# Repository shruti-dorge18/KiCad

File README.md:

# 📐KiCad PCB Design Projects

A collection of PCB designs created using **KiCad**, covering schematic design, PCB layout, footprint integration, and 3D visualization.

## 🛠️ Tools 

**KiCad**

## 🔗 Boardrepo 

PCB designs are also uploaded to **Boardrepo** for easy viewing without downloading or installing KiCad.

View my Boardrepo profile: https://boardrepo.com/shruti-dorge18

Each project in this repository includes its corresponding **Boardrepo link** for viewing the PCB design.

## 📋 Repository Contents 

Each project may include:

* `.kicad_sch` — Schematic
* `.kicad_pcb` — PCB layout
* `.kicad_pro` — KiCad project file
* Images — Schematic, PCB layout, and 3D views
* Footprints

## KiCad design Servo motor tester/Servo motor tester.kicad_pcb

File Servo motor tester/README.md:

# Servo Motor Tester – PCB Design

A PCB design for a servo motor tester circuit, created using KiCad.

## Overview

Designed a 555-timer-based PWM servo motor tester with an adjustable potentiometer for varying the PWM signal to sweep it through its range of motion.

The project was developed to practice PCB designing.

## Tools Used

* KiCad
* Snapmagic :  for downloading footprint & 3D model of potentiometer

## View PCB on Boardrepo
https://boardrepo.com/shruti-dorge18/servo-motor-tester

## Reference

This project was created while following this YouTube tutorial by Ampnics, for learning and reference:

https://youtu.be/3BYGPpejStI?si=WuTzUE_sMDbFLJ6_

## Project Structure

```text
Servo motor tester/
├── 3D model of potentiometer/
│   └── RD901F-40-15R1-B100K-00DL1.step
├── Footprints.pretty/
│   └── POT_RD901F-40-15R1-B100K-00DL1.kicad_mod
├── Images/
│   ├── 3Dview.png
│   ├── pcb.png
│   └── schematic.png
├── Servo motor tester.kicad_pcb
├── Servo motor tester.kicad_pro
└── Servo motor tester.kicad_sch
```

## Files

| File / Folder  | Description                                                   |
| -------------- | ------------------------------------------------------------- |
| `.kicad_sch`   | Circuit schematic                                             |
| `.kicad_pcb`   | PCB layout                                                    |
| `.kicad_pro`   | KiCad project file                                            |
| `Images/`      | Project images showing the schematic, PCB layout, and 3D view |

## Components used

* NE555P Timer IC
* Resistors (x3)
* Unpolarized capacitor 
* 1N4148 diode
* LED 
* Potentiometer
* Connector header pins ( 01x02 pin for power supply)
* Connector header pins ( 01x03 pin for connecting servo motor )

## How to Open

1. Clone or download this repository.
2. Open the KiCad project file:

```text
Servo_motor_tester.kicad_pro
```

3. Open the schematic or PCB Editor from KiCad.
4. Use **View → 3D Viewer** to inspect the PCB in 3D.

## Schematic

## PCB Layout

## 3D View

## Author

**Shruti Dorge**

---

*Designed using KiCad.*

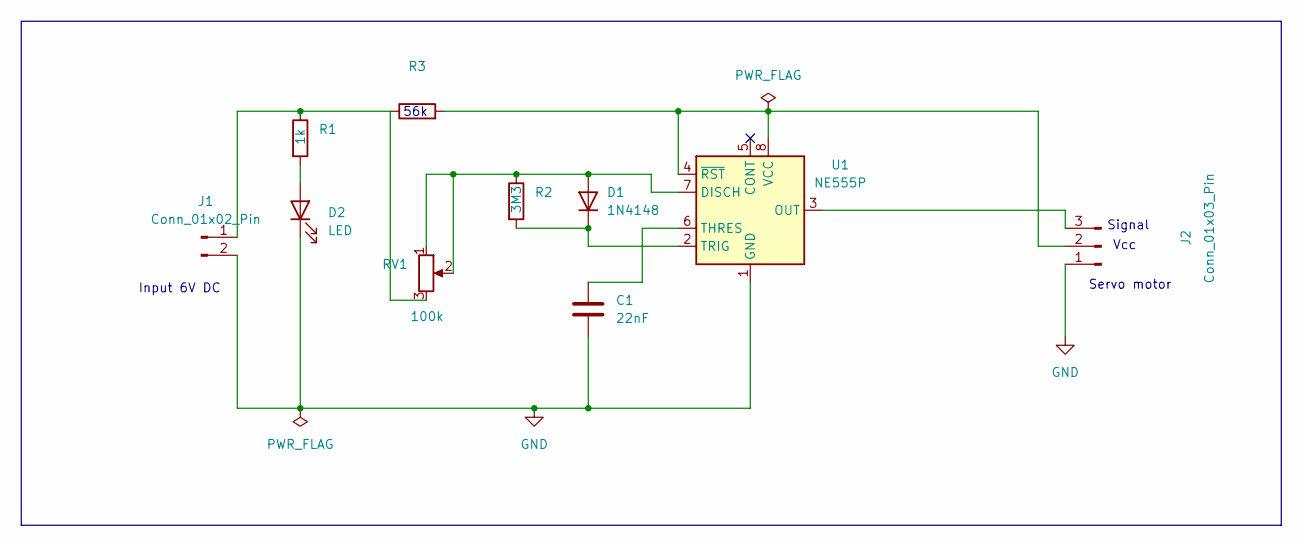
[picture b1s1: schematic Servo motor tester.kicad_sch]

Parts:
C1: 22nF; C_Disc_D4.3mm_W1.9mm_P5.00mm
D1: 1N4148; D_DO-35_SOD27_P7.62mm_Horizontal
D2: LED; LED_D3.0mm
J1: Conn_01x02_Pin; PinHeader_1x02_P2.54mm_Horizontal
J2: Conn_01x03_Pin; PinHeader_1x03_P2.54mm_Horizontal
R1: 1k; R_Axial_DIN0204_L3.6mm_D1.6mm_P7.62mm_Horizontal
R2: 3M3; R_Axial_DIN0204_L3.6mm_D1.6mm_P7.62mm_Horizontal
R3: 56k; R_Axial_DIN0204_L3.6mm_D1.6mm_P7.62mm_Horizontal
RV1: 100k; POT_RD901F-40-15R1-B100K-00DL1
U1: NE555P; DIP-8_W7.62mm

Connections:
GND: C1.2, D2.1 (K), J1.2, J2.1, U1.1 (GND)
unnamed: D1.2 (A), R2.1, RV1.1, RV1.2, U1.7 (DISCH)
unnamed: D1.1 (K), R2.2, U1.2 (TRIG)
unnamed: D2.2 (A), R1.2
unnamed: J1.1, R1.1, R3.1, RV1.3
unnamed: J2.2, R3.2, U1.4 (~RST), U1.8 (VCC)
unnamed: J2.3, U1.3 (OUT)
unnamed: C1.1, U1.6 (THRES)

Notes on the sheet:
Input 6V DC
Vcc
56k
Signal
Servo motor

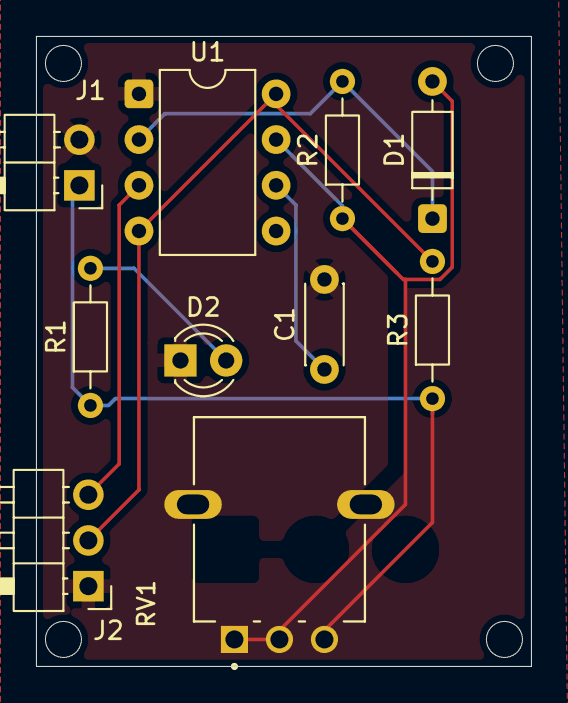
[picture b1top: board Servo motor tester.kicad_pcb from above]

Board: 2 copper layers, 27.5 x 35.0 mm, 10 parts (0 on the bottom side), 8 nets.

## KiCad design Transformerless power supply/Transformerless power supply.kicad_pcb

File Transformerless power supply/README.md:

# Transformerless Power Supply – PCB Design

A PCB design for a transformerless power supply, created using KiCad.

## Overview

Designed a transformerless AC–DC power supply to convert AC input into a lower, regulated DC output for low-power electronic circuits;

integrating bridge rectification, filtering, Zener-based voltage regulation, LM7805 regulation, and LED indication.

The project was developed to practice PCB designing

## Tools Used

* KiCad

## View PCB on Boardrepo
https://boardrepo.com/shruti-dorge18/transformerless-power-supply

## Reference

This project was created while following this YouTube tutorial for learning and reference:

https://youtu.be/qJ6HhyoyFbA?si=Ja4rXb8v6HYuZlvf

## Project Structure

```text
Transformerless_power_supply/
├── Transformerless_power_supply.kicad_pcb
├── Transformerless_power_supply.kicad_pro
├── Transformerless_power_supply.kicad_sch
├── Images/
    ├── Transformerless_power_supply_schematic.png
    ├── Transformerless_power_supply_pcb.png
    └── Transformerless_power_supply_3Dview.png

```

## Files

| File / Folder | Description                                                   |
| ------------- | ------------------------------------------------------------- |
| `.kicad_sch`  | Circuit schematic                                             |
| `.kicad_pcb`  | PCB layout                                                    |
| `.kicad_pro`  | KiCad project file                                            |
| `Images/`     | Project images showing the schematic, PCB layout, and 3D view |

## PCB Design

The PCB was designed using KiCad with through-hole components and routed connections.

The PCB layout includes components such as:

* 1N4007 Diodes (x4)
* Zener diode (x2)
* Resistors (x4)
* Unpolarized capacitor (x2)
* Polarized capacitor (x2)
* LED
* Terminal blocks (x2)
* LM7805_TO220 Voltage regulator 

## How to Open

1. Clone or download this repository.
2. Open the KiCad project file:

```text
Transformerless_power_supply.kicad_pro
```

3. Open the schematic or PCB Editor from KiCad.
4. Use **View → 3D Viewer** to inspect the PCB in 3D.

## Schematic

## PCB Layout

## 3D View

## Author

**Shruti Dorge**

---

*Designed using KiCad.*

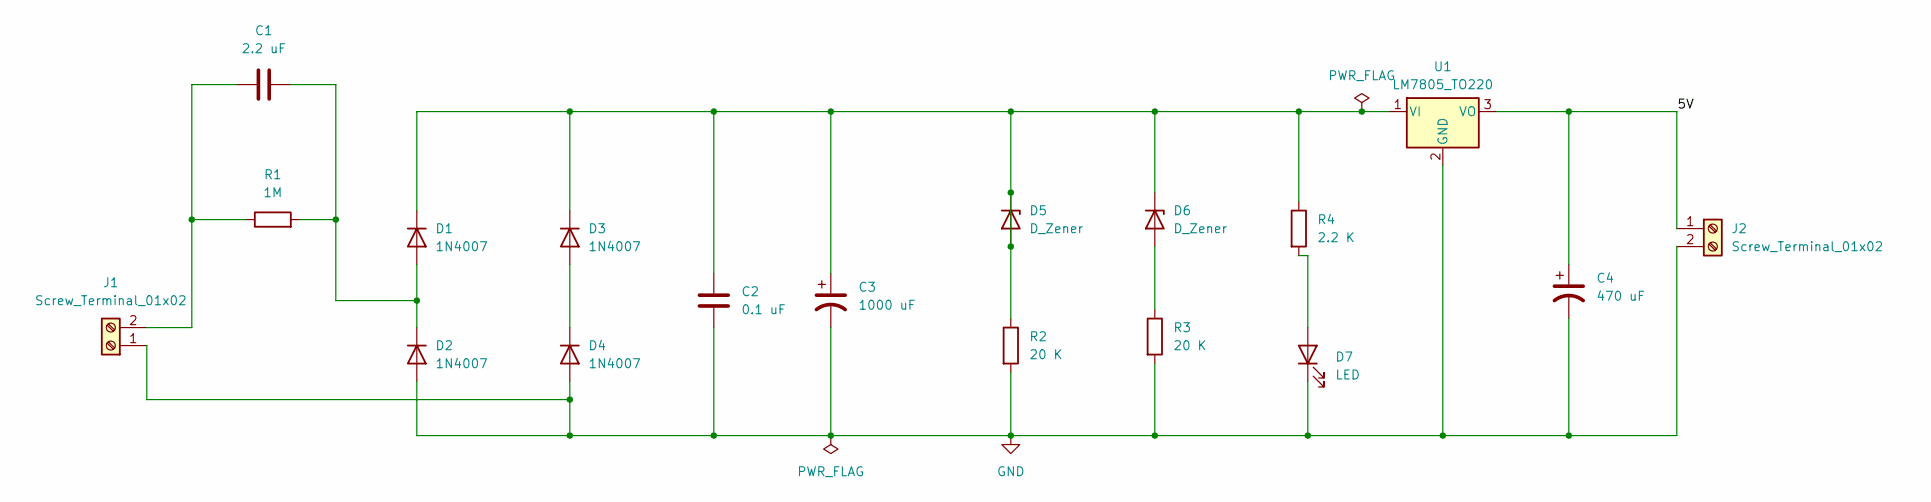
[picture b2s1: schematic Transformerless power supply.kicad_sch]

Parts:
C1: 2.2 uF; C_Rect_L18.0mm_W6.0mm_P15.00mm_FKS3_FKP3
C2: 0.1 uF; C_Disc_D4.7mm_W2.5mm_P5.00mm
C3: 1000 uF; CP_Radial_D10.0mm_P5.00mm
C4: 470 uF; CP_Radial_D10.0mm_P3.80mm
D1, D2, D3, D4: 1N4007; D_DO-41_SOD81_P10.16mm_Horizontal
D5, D6: D_Zener; D_A-405_P7.62mm_Horizontal
D7: LED; LED_D5.0mm
J1, J2: Screw_Terminal_01x02; TerminalBlock_CUI_TB007-508-02_1x02_P5.08mm_Horizontal
R1: 1M; R_Axial_DIN0207_L6.3mm_D2.5mm_P7.62mm_Horizontal
R2, R3: 20 K; R_Axial_DIN0207_L6.3mm_D2.5mm_P7.62mm_Horizontal
R4: 2.2 K; R_Axial_DIN0207_L6.3mm_D2.5mm_P7.62mm_Horizontal
U1: LM7805_TO220; TO-220-3_Vertical

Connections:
/5V: C4.1, J2.1, U1.3 (VO)
GND: C2.2, C3.2, C4.2, D2.2 (A), D4.2 (A), D7.1 (K), J1.1, J2.2, R2.2, R3.2, U1.2 (GND)
unnamed: C1.2, D1.2 (A), D2.1 (K), R1.2
unnamed: C2.1, C3.1, D1.1 (K), D3.1 (K), D5.1 (K), D5.2 (A), D6.1 (K), R2.1, R4.1, U1.1 (VI)
unnamed: D3.2 (A), D4.1 (K)
unnamed: D6.2 (A), R3.1
unnamed: D7.2 (A), R4.2
unnamed: C1.1, J1.2, R1.1

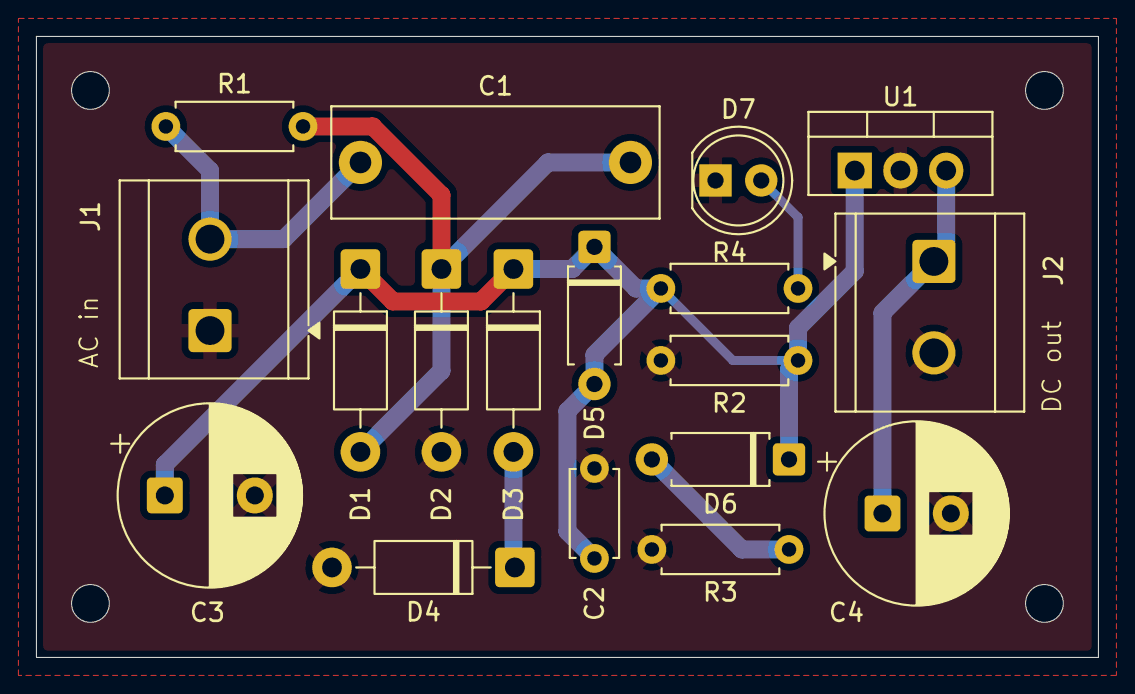
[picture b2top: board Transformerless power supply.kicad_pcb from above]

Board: 2 copper layers, 59.0 x 34.5 mm, 18 parts (0 on the bottom side), 8 nets.

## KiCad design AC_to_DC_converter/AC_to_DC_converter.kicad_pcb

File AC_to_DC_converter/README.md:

# AC to DC Converter – PCB Design

A PCB design for an AC to DC converter, created using KiCad.

## Overview

Designed an AC–DC conversion circuit to convert AC input into regulated DC output ;

using a bridge rectifier (1N4007), filtering capacitor, current-limiting resistors, and LED power indication.

The project was developed to practice pcb designing

## Tools Used

* KiCad

## View PCB on Boardrepo
https://boardrepo.com/shruti-dorge18/ac-to-dc-converter

## Reference

This project was created while following this YouTube tutorial for learning and reference:

https://youtu.be/dsz6Dzvou2o?si=fpQfjwIH6Eks47Hm

## Project Structure

```text
AC_to_DC_converter/
├── AC_to_DC_converter.kicad_pcb
├── AC_to_DC_converter.kicad_pro
├── AC_to_DC_converter.kicad_sch
└── 3dmodels/
    ├── Capacitor_THT.3dshapes/
    ├── Diode_THT.3dshapes/
    ├── LED_THT.3dshapes/
    └── Resistor_THT.3dshapes/
```

## Files

| File / Folder | Description                             |
| ------------- | --------------------------------------- |
| `.kicad_sch`  | Circuit schematic                       |
| `.kicad_pcb`  | PCB layout                              |
| `.kicad_pro`  | KiCad project file                      |
| `3dmodels/`   | Project-local 3D models used by the PCB |

## PCB Design

The PCB was designed using KiCad with through-hole components and routed connections.

The PCB layout includes components such as:

* 1N4007 Diodes (x4)
* Resistors (x2)
* Unpolarized capacitor
* LED
* Terminal blocks (x2)

## 3D Models

The required component 3D models are included in the project under the `3dmodels/` directory.

The PCB uses project-local paths for these models, making the project more portable when shared with others.

## How to Open

1. Clone or download this repository.
2. Open the KiCad project file:

```text
AC_to_DC_converter.kicad_pro
```

3. Open the schematic or PCB Editor from KiCad.
4. Use **View → 3D Viewer** to inspect the PCB in 3D.

## Schematic

## PCB Layout

## 3D View

## Author

**Shruti Dorge**

---

*Designed using KiCad.*

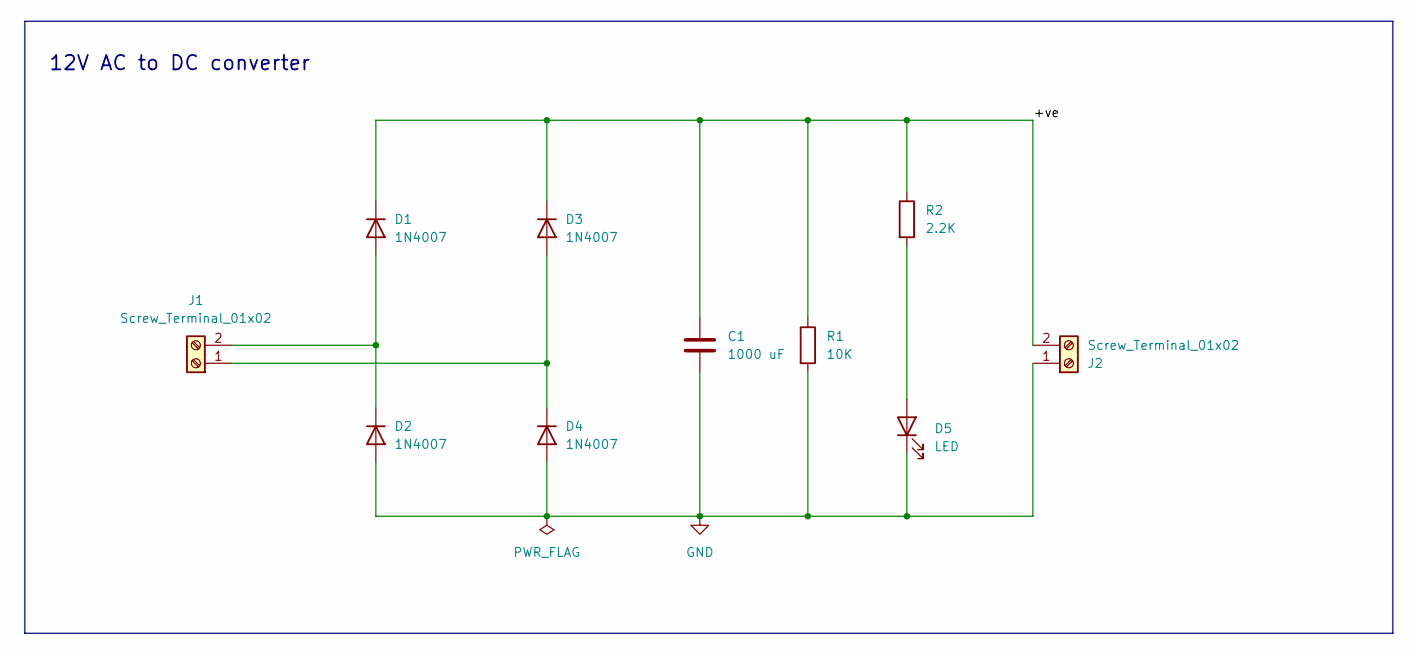
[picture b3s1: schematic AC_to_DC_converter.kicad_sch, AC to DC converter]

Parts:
C1: 1000 uF; C_Radial_D8.0mm_H11.5mm_P3.50mm
D1, D2, D3, D4: 1N4007; D_DO-41_SOD81_P10.16mm_Horizontal
D5: LED; LED_D5.0mm
J1, J2: Screw_Terminal_01x02; TerminalBlock_CUI_TB007-508-02_1x02_P5.08mm_Horizontal
R1: 10K; R_Axial_DIN0204_L3.6mm_D1.6mm_P7.62mm_Horizontal
R2: 2.2K; R_Axial_DIN0204_L3.6mm_D1.6mm_P7.62mm_Horizontal

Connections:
/+ve: C1.1, D1.1 (K), D3.1 (K), J2.2, R1.1, R2.1
GND: C1.2, D2.2 (A), D4.2 (A), D5.1 (K), J2.1, R1.2
unnamed: D1.2 (A), D2.1 (K), J1.2
unnamed: D3.2 (A), D4.1 (K), J1.1
unnamed: D5.2 (A), R2.2

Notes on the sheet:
12V AC to DC converter

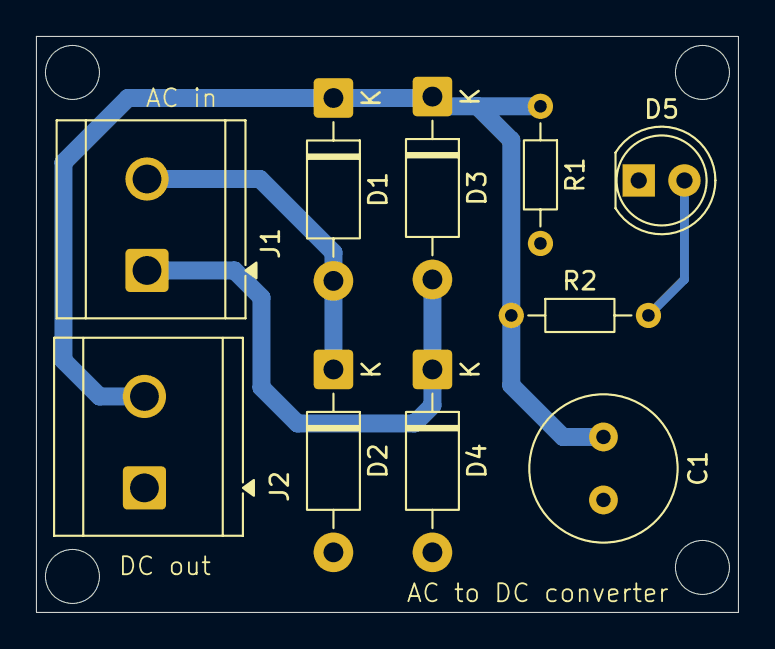
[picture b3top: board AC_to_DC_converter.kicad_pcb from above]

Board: 2 copper layers, 39.0 x 32.0 mm, 10 parts (0 on the bottom side), 5 nets.
